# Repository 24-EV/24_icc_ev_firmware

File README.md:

# 24 INHA EV 데이터 로깅 앱 사용법  

### 완성도를 높이기 위하여 조금씩 수정 예정입니다. 업데이트 날짜 확인하여 이전의 코드, 방식과의 차이점 파악 후 진행해주세요.

### 깃허브 레포지토리 주소

클라이언트 : https://github.com/nitepp04/24_icc_ev_client

서버 : https://github.com/nitepp04/24_icc_ev_server

펌웨어 : https://github.com/nitepp04/24_icc_ev_firmware

## 주요 기능

- 차량의 컨트롤러 및 모듈에서 오는 데이터 값을 시각화
    - 현재 받는 데이터
        - timestamp
            - Real TIme Clock 모듈
            - 당시 RTC 모듈 고장으로 인하여 서버의 시간으로 대체함
            - 복구 원할 시 서버 코드 수정 필요
        - RPM
        - MOTOR_CURRENT
        - BATTERY_VOLTAGE
        - THROTTLE_SIGNAL
        - CONTROLLER_TEMPERATURE
        - SPEED
            - 클라이언트에선 velocity라는 키값으로 사용됨
        - BATTERY_PERCENT
        - lat, lng
            - GPS 모듈 고장
            - 클라이언트 코드에는 구현되어 있으나, 서버 코드에서 삭제함.
            - 복구 원할 시 서버 코드 수정 필요
- 차량 현재 위치 시각화
    - 카카오맵 API를 통하여 차량의 현재 위치를 시각화한다.
- Excel 데이터 다운로드
    - 원하는 시간대의 데이터를 DB에서 불러와 액셀 파일로 다운로드

## 용어 정리

- JavaScript : 프로그래밍 언어
- React : JavaScript 기반 UI 라이브러리
- Node.js : JavaScript 실행 환경
    - 브라우저에서만 실행 가능했던 JavaScript를 서버에서도 실행 가능하도록 해줌
- Express : Node.js의 프레임워크. Express 는 Node.js 위에서 동작하는 웹 프레임 워크
- AWS EC2 : 아마존에서 빌려주는 컴퓨터
- AWS DynamoDB : NoSQL 데이터베이스
    - 고정된 테이블 구조를 사용하지 않고, 다양한 데이터 구조를 저장할 수 있는 데이터 베이스.
    - JSON 형식 저장 가능
- JSON : 사람도 기계도 읽기 쉬운 경량 데이터 형식.
- Vercel : 프론트엔드 프로젝트 배포 클라우드 플랫폼으로, 깃허브와 연동하여 코드 푸시 때마다 자동 업데이트.
- Git : 버전 관리 시스템
- GitHub : Git을 온라인에서 저장하고 협업할 수 있는 플랫폼.
    - 코드를 수정할 때마다 git에 업데이트 하거나, 예전 코드로 다시 돌아갈 수 있고, 이를 github에 올려 온라인으로 저장하고 협업할 수 있습니다.
- 터미널 명령어(CLI) : 터미널에서 사용하는 명령어
    - 이제 등장할 cd, chmod, ls 등이 있다.

프로그램 개선을 원할 때, 어떠한 용어가 있는지 알면 도움이 될 거라 생각하여 검색하기 난감할 것 같은 용어들 몇개만 짧게 적어둡니다.

## 설치 및 실행 방법

### 기본 설정

1. AWS 계정 생성 : https://deoking.tistory.com/27
    1. aws.amazon.com/ko/
    2. 관리 잘 하셔야 돼요. 안 그러면 비용 폭탄 맞아요
2. GitHub 계정 생성
    1. github.com
3. VS 코드 설치 및 환경 설정
    1. Visual Studio Code 검색하여 인스톨
    2. 쭉쭉 넘기다가 추가 작업 선택에서 다음과 같이 체크 (권장)

    4. VS 코드를 열어 왼쪽 메뉴바의 Extension → Korean 검색하여 Korean Language Pack for Visual 인스톨
4. 프론트엔드, 백엔드 레포지토리 포크
    1. 현재 문서 상단에 기재되어 있는 프론트엔드, 백엔드의 깃허브 레포지토리 링크로 각각 접속 → 우측 상단의 Fork 버튼 클릭

    2. Owner : 자신 계정, Repository name : 원하는 대로

    3. 자신의 깃허브 레포지토리에 포크된 레포지토리가 잘 생성되었나 체크
    
---

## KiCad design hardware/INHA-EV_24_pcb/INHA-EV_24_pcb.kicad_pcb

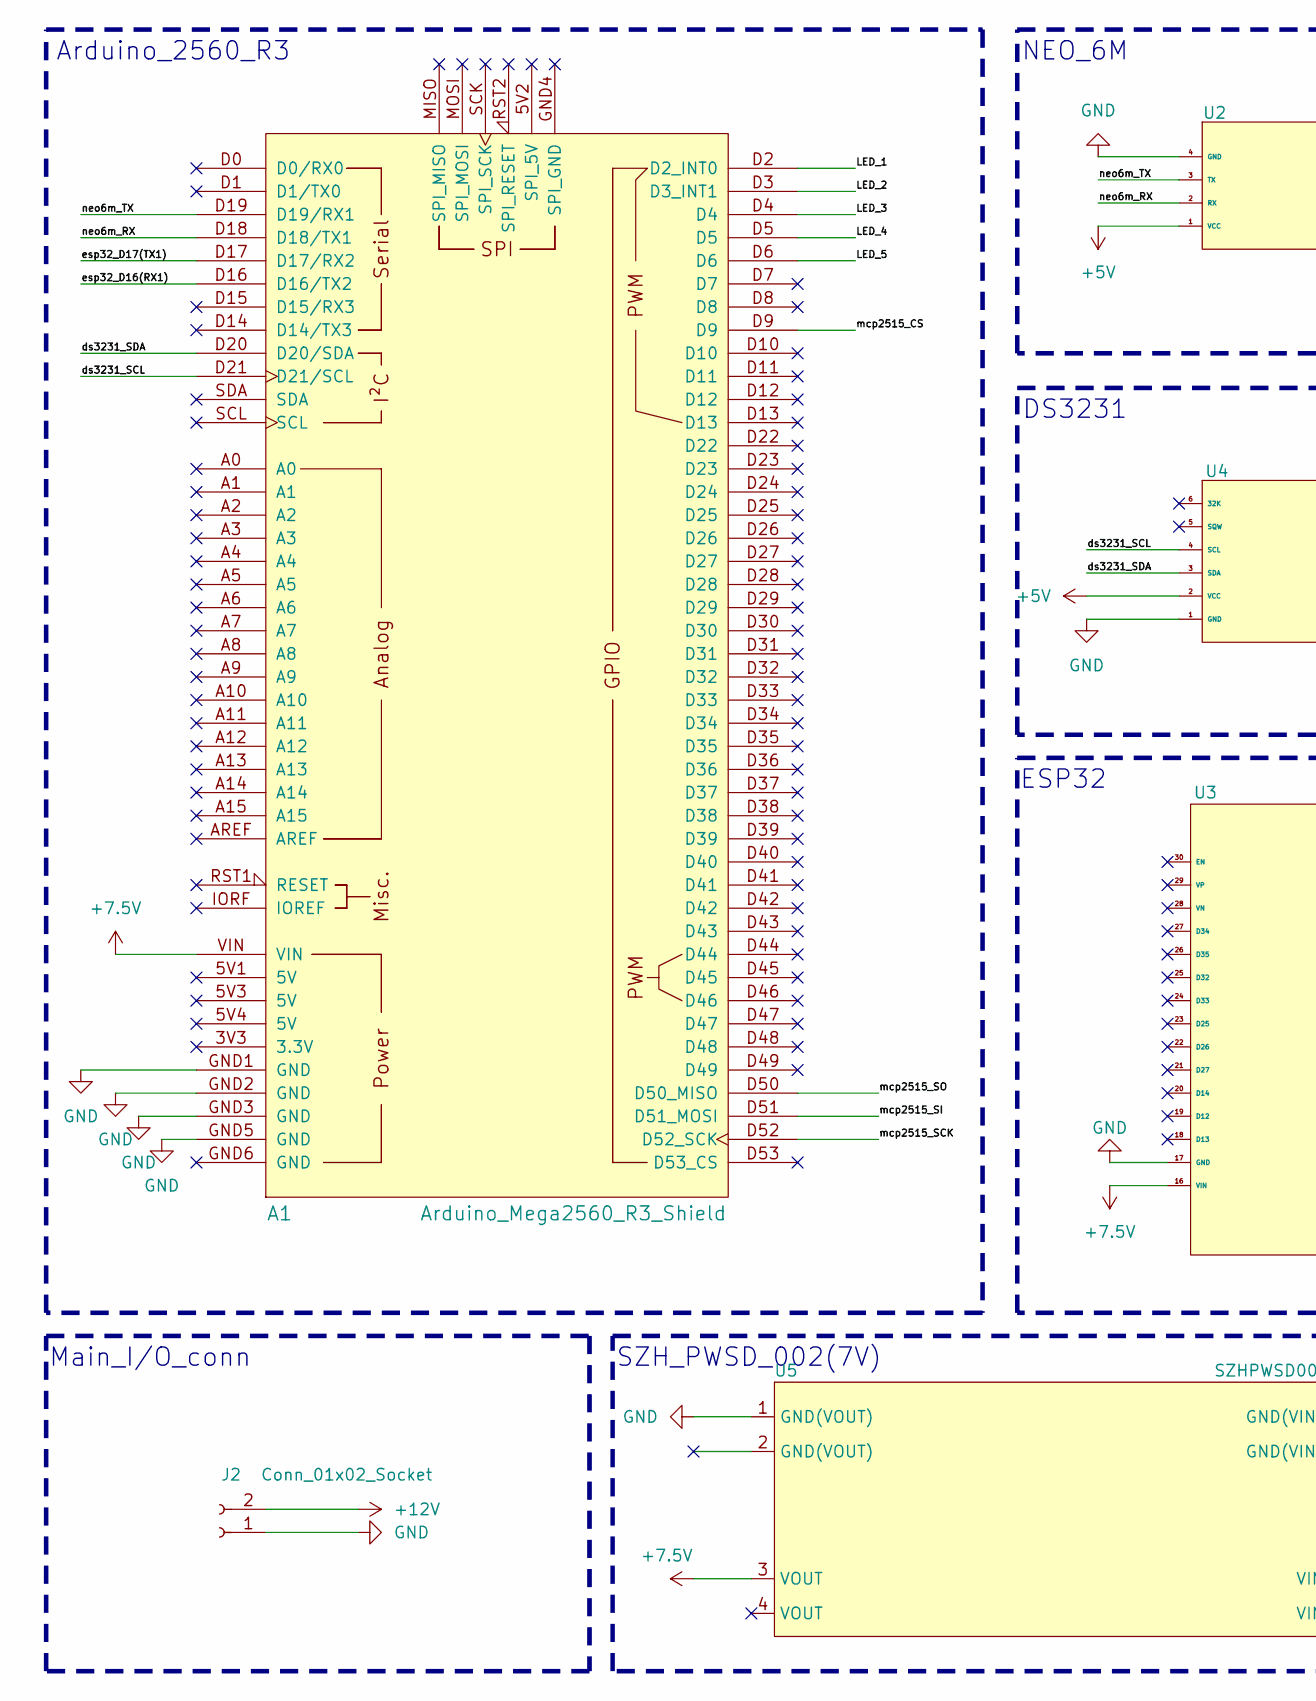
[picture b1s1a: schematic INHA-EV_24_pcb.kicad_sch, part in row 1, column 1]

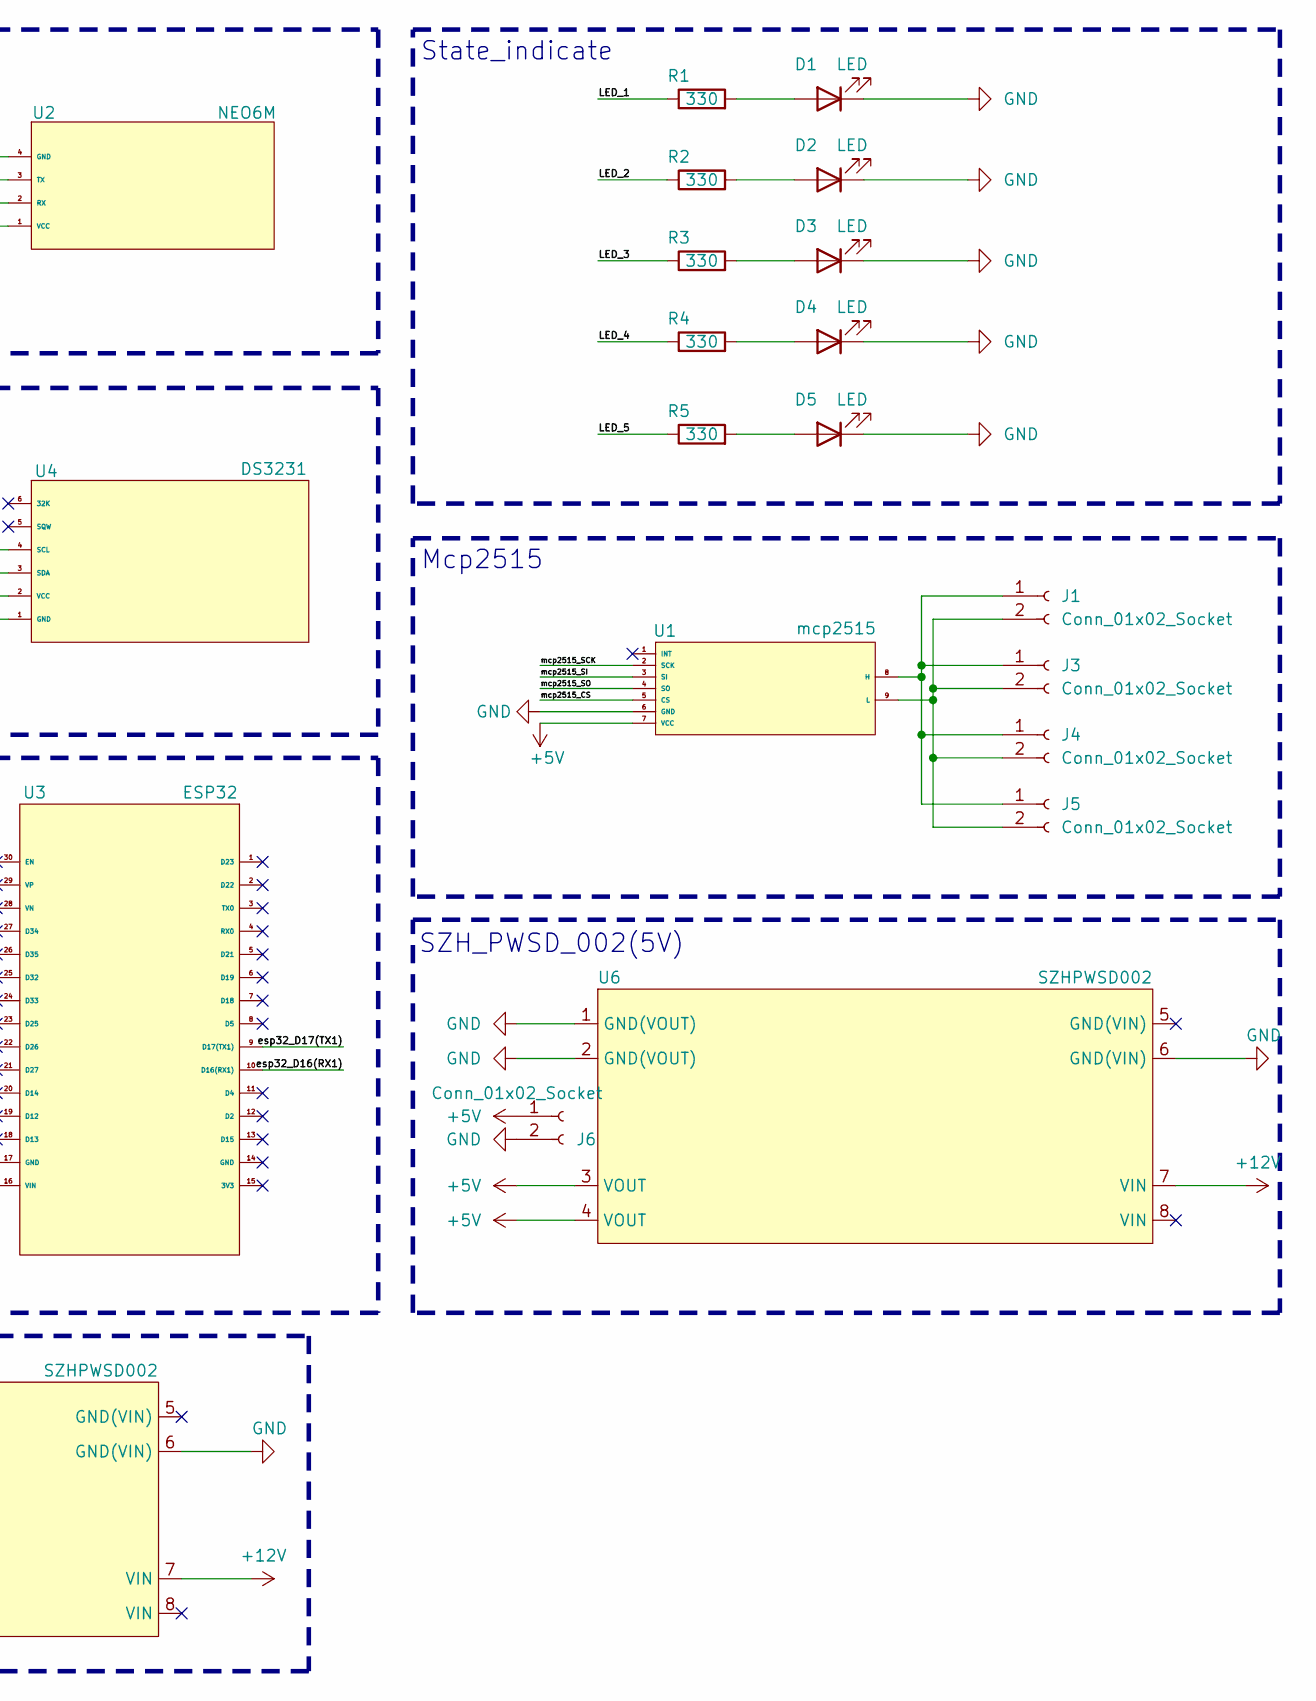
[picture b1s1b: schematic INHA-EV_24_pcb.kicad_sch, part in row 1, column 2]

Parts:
A1: Arduino_Mega2560_R3_Shield
D1, D2, D3, D4, D5: LED; LED_D5.0mm_FlatTop
J1, J2, J3, J4, J5, J6: Conn_01x02_Socket; Molex_KK-254_AE-6410-02A_1x02_P2.54mm_Vertical
R1, R2, R3, R4, R5: 330; R_Axial_DIN0207_L6.3mm_D2.5mm_P10.16mm_Horizontal
U1: mcp2515
U2: NEO6M
U3: ESP32
U4: DS3231
U5, U6: SZHPWSD002; SZHPWSD003

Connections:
+5V: J6.1, U1.7 (VCC), U2.1 (VCC), U4.2 (VCC), U6.3 (VOUT), U6.4 (VOUT)
+7.5V: A1.VIN, U3.16 (VIN), U5.3 (VOUT)
+12V: J2.2, U5.7 (VIN), U6.7 (VIN)
/LED_1: A1.D2 (D2_INT0), R1.1
/LED_2: A1.D3 (D3_INT1), R2.1
/LED_3: A1.D4, R3.1
/LED_4: A1.D5, R4.1
/LED_5: A1.D6, R5.1
/ds3231_SCL: A1.D21 (D21/SCL), U4.4 (SCL)
/ds3231_SDA: A1.D20 (D20/SDA), U4.3 (SDA)
/esp32_D16(RX1): A1.D16 (D16/TX2), U3.10 (D16(RX1))
/esp32_D17(TX1): A1.D17 (D17/RX2), U3.9 (D17(TX1))
/mcp2515_CS: A1.D9, U1.5 (CS)
/mcp2515_SCK: A1.D52 (D52_SCK), U1.2 (SCK)
/mcp2515_SI: A1.D51 (D51_MOSI), U1.3 (SI)
/mcp2515_SO: A1.D50 (D50_MISO), U1.4 (SO)
/neo6m_RX: A1.D18 (D18/TX1), U2.2 (RX)
/neo6m_TX: A1.D19 (D19/RX1), U2.3 (TX)
GND: A1.GND1 (GND), A1.GND2 (GND), A1.GND3 (GND), A1.GND5 (GND), D1.1 (K), D2.1 (K), D3.1 (K), D4.1 (K), D5.1 (K), J2.1, J6.2, U1.6 (GND), U2.4 (GND), U3.17 (GND), U4.1 (GND), U5.1 (GND(VOUT)), U5.6 (GND(VIN)), U6.1 (GND(VOUT)), U6.2 (GND(VOUT)), U6.6 (GND(VIN))
unnamed: D1.2 (A), R1.2
unnamed: D2.2 (A), R2.2
unnamed: D3.2 (A), R3.2
unnamed: D4.2 (A), R4.2
unnamed: D5.2 (A), R5.2
unnamed: J1.1, J3.1, J4.1, J5.1, U1.8 (H)
unnamed: J1.2, J3.2, J4.2, J5.2, U1.9 (L)

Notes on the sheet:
SZH_PWSD_002(5V)
Main_I/O_conn
SZH_PWSD_002(7V)
ESP32
Mcp2515
DS3231
Arduino_2560_R3
NEO_6M
State_indicate

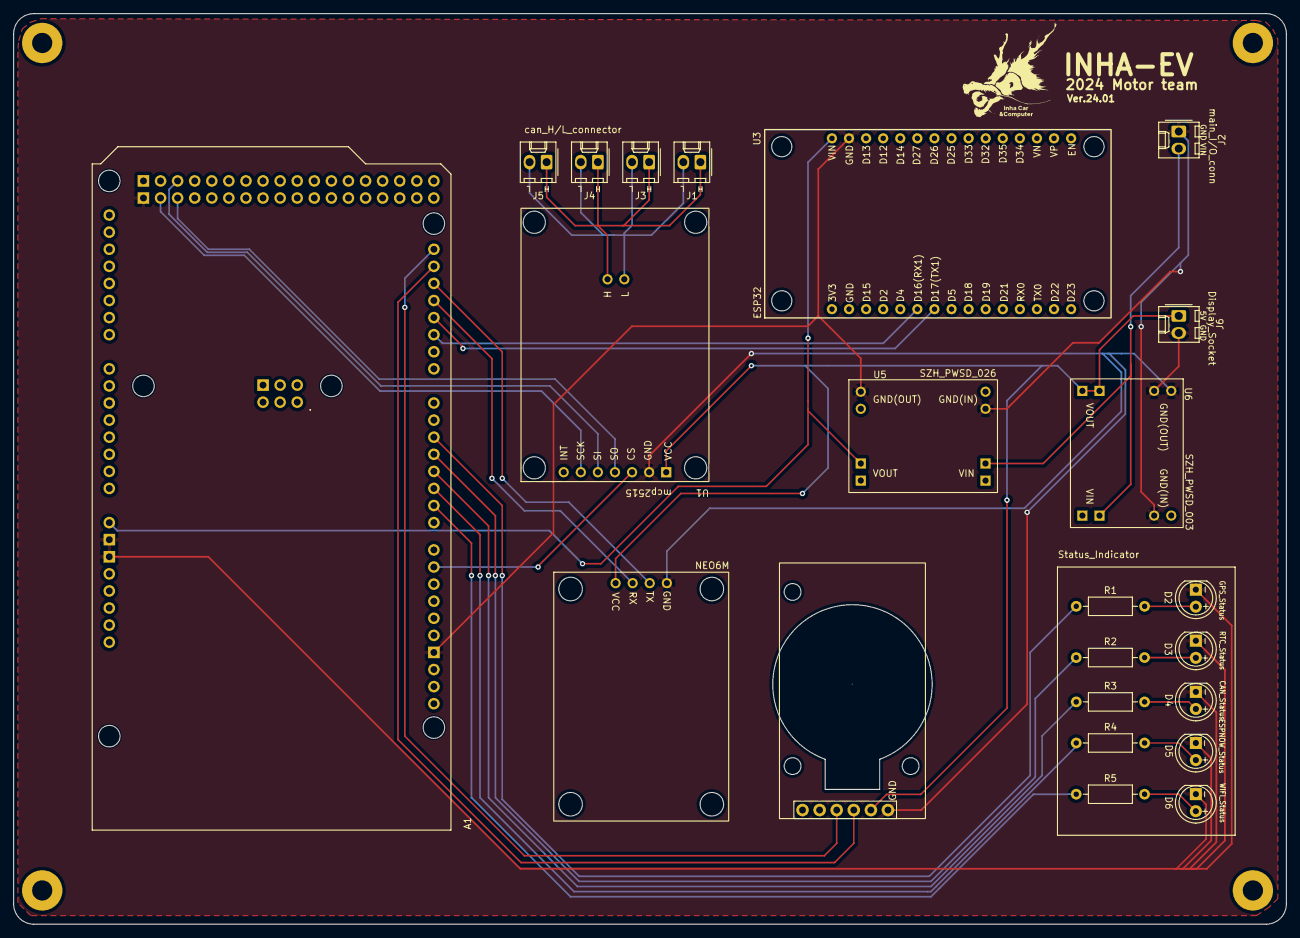
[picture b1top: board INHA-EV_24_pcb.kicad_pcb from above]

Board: 2 copper layers, 189.2 x 135.4 mm, 23 parts (1 on the bottom side), 26 nets.

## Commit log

2025-03-12 fix: pcb foldering
2025-03-12 docs : README.md 업데이트
2025-07-23 feat : 25년도 새 컨트롤러에 맞는 데이터 버퍼 처리
    25년도 컨트롤러는 기존과 다른 방식의 데이터 값을 주기에 거기에 맞는 데이터 버퍼를 처리하도록 코드를 수정함.
    코드 작성 시에 테스트 진행 환경이 갖추어지지 않았기에, 정상작동하는지는 모름 ..
